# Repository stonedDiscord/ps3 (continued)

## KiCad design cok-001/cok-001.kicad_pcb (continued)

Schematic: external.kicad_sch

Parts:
C3246: 47u 25V; CP_EIA-3528-15_AVX-H
C3247: 47u 25V; CP_EIA-7132-28_AVX-C
D3201, D3202, D3203, D3204, D3205, D3206, D3207, D3208: Dual diode; SC-82AA
FB3206: FerriteBead_Small
J3208: 凸; Molex_SlimStack_55560-0801_2x40_P0.50mm_Vertical
J3209: ATA Power; JST_PH_S4B-PH-SM4-TB_1x04-1MP_P2.00mm_Horizontal
J3219: for Multi_Card_Board; Hirose_FH12-15S-0.5SH_1x15-1MP_P0.50mm_Horizontal
J3221: IMSA-9637S-60Y801; Hirose_FH12-60S
LF3204: 0uH
Q3201: DTC144E; SOT-323_SC-70
R3211, R3212, R3213, R3214, R3215, R3216, R3217, R3218, R3219, R3220, R3221, R3222, R3223, R3224, R3225, R3226, R3227, R3231, R3282, R3283, R3284, R3285, R3286, R3287, R3298: 0; R_0402_1005Metric
R3228: 82; R_0402_1005Metric
R3229, R3230, R3232: 22; R_0402_1005Metric
R3233, R3234, R3236, R3237, R3238, R3239: 33; R_0402_1005Metric
R3240, R3253: 0; R_0603_1608Metric
R3241: XX; R_0603_1608Metric; not fitted
R3247: 10k; R_0402_1005Metric
R3297: 0; R_0805_2012Metric
RN3201, RN3202, RN3203, RN3204, RN3205, RN3206, RN3207, RN3208, RN3209, RN3210, RN3211: 56; R_Array_Convex_4x0402
TP3222: TestPoint; TestPoint_Pad_1.0x1.0mm

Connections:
+3.3V_BRIDGE: R3240.1; also elsewhere on the board
/External/SB_USB2_DM_32: J3219.4, LF3204.4
/External/SB_USB2_DP_32: J3219.3, LF3204.2
/External/XSB_CBLID: J3221.43, Q3201.1 (B)
BD_LED: J3221.50; also elsewhere on the board
DISC_CHUCK: R3286.1; also elsewhere on the board
DISC_IN: R3287.1
DISC_IN_MECHA: J3221.55; also elsewhere on the board
DISC_OUT8_SW: R3285.1
DISC_OUT12_SW: R3284.1
EJECT_MECHA: J3221.56; also elsewhere on the board
GND: C3246.2, C3247.2, D3201.1 (A1), D3201.2 (A2), D3202.1 (A1), D3202.2 (A2), D3203.1 (A1), D3203.2 (A2), D3204.1 (A1), D3204.2 (A2), D3205.1 (A1), D3205.2 (A2), D3206.1 (A1), D3206.2 (A2), D3207.1 (A1), D3207.2 (A2), D3208.1 (A1), D3208.2 (A2), J3208.2, J3208.11, J3208.12, J3208.18, J3208.21, J3208.22, J3208.35, J3208.36, J3208.47, J3208.48, J3208.61, J3208.62, J3208.71, J3208.72, J3209.2, J3209.3, J3209.MP (MountPin), J3219.1, J3219.2, J3219.5, J3219.6, J3219.8, J3219.13, J3219.15, J3219.MP (MountPin), J3221.2, J3221.19, J3221.21, J3221.23, J3221.25, J3221.27, J3221.29, J3221.38, J3221.42, J3221.51, J3221.59, Q3201.2 (E), R3247.1; also elsewhere on the board
MC_ALIVE: R3282.1; also elsewhere on the board
MC_P_OFF_REQ: J3221.48; also elsewhere on the board
MC_RESERVED: J3221.49
MECHA_INT: R3283.1; also elsewhere on the board
unnamed: J3208.1, R3241.2
unnamed: C3247.1, J3209.1, R3297.2
unnamed: C3246.1, J3209.4
unnamed: J3219.7, R3253.2
unnamed: FB3206.2, J3219.9, J3219.10, J3219.11, J3219.12
unnamed: J3221.1, R3211.2
unnamed: J3221.3, R3227.2
unnamed: J3221.4, R3226.2
unnamed: J3221.5, R3225.2
unnamed: J3221.6, R3224.2
unnamed: J3221.7, R3223.2
unnamed: J3221.8, R3222.2
unnamed: J3221.9, R3221.2
unnamed: J3221.10, R3220.2
unnamed: J3221.11, R3219.2
unnamed: J3221.12, R3218.2
unnamed: J3221.13, R3217.2
unnamed: J3221.14, R3216.2
unnamed: J3221.15, R3215.2
unnamed: J3221.16, R3214.2
unnamed: J3221.17, R3213.2
unnamed: J3221.18, R3212.2
unnamed: J3221.20, R3232.2
unnamed: J3221.22, R3231.2
unnamed: J3221.24, R3230.2
unnamed: J3221.26, R3229.2
unnamed: J3221.28, R3228.2
unnamed: J3221.31, R3239.2
unnamed: J3221.32, R3238.2
unnamed: J3221.33, R3237.2
unnamed: J3221.34, R3236.2
unnamed: J3221.36, R3234.2
unnamed: J3221.37, R3233.2
unnamed: J3221.44, TP3222.1 (1_1)
unnamed: J3221.46, R3283.2
unnamed: J3221.47, R3282.2
unnamed: J3221.52, R3287.2
unnamed: J3221.54, R3286.2
unnamed: J3221.57, R3285.2
unnamed: J3221.58, R3284.2
unnamed: R3240.2, R3241.1
PHOTO_LED: J3221.53
SB_ATA0_CS0: R3238.1
SB_ATA0_CS1: R3239.1
SB_ATA0_DA0: R3236.1
SB_ATA0_DA1: R3234.1; also elsewhere on the board
SB_ATA0_DA2: R3237.1
SB_ATA0_DASP: J3221.30
SB_ATA0_DD0: D3201.3 (K1), R3226.1; also elsewhere on the board
SB_ATA0_DD1: D3201.4 (K2), R3224.1; also elsewhere on the board
SB_ATA0_DD2: D3203.3 (K1), R3222.1; also elsewhere on the board
SB_ATA0_DD3: D3203.4 (K2), R3220.1; also elsewhere on the board
SB_ATA0_DD4: D3204.3 (K1), R3218.1; also elsewhere on the board
SB_ATA0_DD5: D3204.4 (K2), R3216.1; also elsewhere on the board
SB_ATA0_DD6: D3205.3 (K1), R3214.1; also elsewhere on the board
SB_ATA0_DD7: D3205.4 (K2), R3212.1; also elsewhere on the board
SB_ATA0_DD8: D3207.4 (K2), R3213.1; also elsewhere on the board
SB_ATA0_DD9: D3207.3 (K1), R3215.1; also elsewhere on the board
SB_ATA0_DD10: D3206.4 (K2), R3217.1; also elsewhere on the board
SB_ATA0_DD11: D3202.4 (K2), R3219.1; also elsewhere on the board
SB_ATA0_DD12: D3202.3 (K1), R3221.1; also elsewhere on the board
SB_ATA0_DD13: D3206.3 (K1), R3223.1; also elsewhere on the board
SB_ATA0_DD14: D3208.4 (K2), R3225.1; also elsewhere on the board
SB_ATA0_DD15: D3208.3 (K1), R3227.1; also elsewhere on the board
SB_ATA0_DIOR: R3230.1
SB_ATA0_DIOW: R3229.1
SB_ATA0_DMACK: R3232.1
SB_ATA0_DMARQ: R3228.1
SB_ATA0_INTRQ: R3233.1; also elsewhere on the board
SB_ATA0_IORDY: R3231.1
SB_ATA0_PDIAG: Q3201.3 (C)
SB_PCI0_CLK: J3208.20; also elsewhere on the board
SB_PCI_AD0: J3208.75, RN3204.8 (R1.2); also elsewhere on the board
SB_PCI_AD0_SB: RN3204.1 (R1.1); also elsewhere on the board
SB_PCI_AD1: J3208.78, RN3209.2 (R2.1); also elsewhere on the board
SB_PCI_AD1_SB: RN3209.7 (R2.2); also elsewhere on the board
SB_PCI_AD2: J3208.73, RN3204.7 (R2.2); also elsewhere on the board
SB_PCI_AD2_SB: RN3204.2 (R2.1); also elsewhere on the board
SB_PCI_AD3: J3208.76, RN3209.3 (R3.1); also elsewhere on the board
SB_PCI_AD3_SB: RN3209.6 (R3.2); also elsewhere on the board
SB_PCI_AD4: J3208.69, RN3204.6 (R3.2); also elsewhere on the board
SB_PCI_AD4_SB: RN3204.3 (R3.1); also elsewhere on the board
SB_PCI_AD5: J3208.74, RN3209.4 (R4.1); also elsewhere on the board
SB_PCI_AD5_SB: RN3209.5 (R4.2); also elsewhere on the board
SB_PCI_AD6: J3208.67, RN3204.5 (R4.2); also elsewhere on the board
SB_PCI_AD6_SB: RN3204.4 (R4.1); also elsewhere on the board
SB_PCI_AD7: J3208.70, RN3211.1 (R1.1); also elsewhere on the board
SB_PCI_AD7_SB: RN3211.8 (R1.2); also elsewhere on the board
SB_PCI_AD8: J3208.68, RN3211.2 (R2.1); also elsewhere on the board
SB_PCI_AD8_SB: RN3211.7 (R2.2); also elsewhere on the board
SB_PCI_AD9: J3208.63, RN3203.7 (R2.2); also elsewhere on the board
SB_PCI_AD9_SB: RN3203.2 (R2.1); also elsewhere on the board
SB_PCI_AD10: J3208.66, RN3211.3 (R3.1); also elsewhere on the board
SB_PCI_AD10_SB: RN3211.6 (R3.2); also elsewhere on the board
SB_PCI_AD11: J3208.59, RN3203.6 (R3.2); also elsewhere on the board
SB_PCI_AD11_SB: RN3203.3 (R3.1); also elsewhere on the board
SB_PCI_AD12: J3208.64, RN3211.4 (R4.1); also elsewhere on the board
SB_PCI_AD12_SB: RN3211.5 (R4.2); also elsewhere on the board
SB_PCI_AD13: J3208.57, RN3203.5 (R4.2); also elsewhere on the board
SB_PCI_AD13_SB: RN3203.4 (R4.1); also elsewhere on the board
SB_PCI_AD14: J3208.60, RN3210.1 (R1.1); also elsewhere on the board
SB_PCI_AD14_SB: RN3210.8 (R1.2); also elsewhere on the board
SB_PCI_AD15: J3208.55, RN3205.8 (R1.2); also elsewhere on the board
SB_PCI_AD15_SB: RN3205.1 (R1.1); also elsewhere on the board
SB_PCI_AD16: J3208.43; also elsewhere on the board
SB_PCI_AD17: J3208.44, RN3208.3 (R3.1); also elsewhere on the board
SB_PCI_AD17_SB: RN3208.6 (R3.2); also elsewhere on the board
SB_PCI_AD18: J3208.41, RN3202.8 (R1.2); also elsewhere on the board
SB_PCI_AD18_SB: RN3202.1 (R1.1); also elsewhere on the board
SB_PCI_AD19: J3208.42, RN3208.4 (R4.1); also elsewhere on the board
SB_PCI_AD19_SB: RN3208.5 (R4.2); also elsewhere on the board
SB_PCI_AD20: J3208.39, RN3202.7 (R2.2); also elsewhere on the board
SB_PCI_AD20_SB: RN3202.2 (R2.1); also elsewhere on the board
SB_PCI_AD21: J3208.40, RN3207.1 (R1.1); also elsewhere on the board
SB_PCI_AD21_SB: RN3207.8 (R1.2); also elsewhere on the board
SB_PCI_AD22: J3208.37, RN3202.6 (R3.2); also elsewhere on the board
SB_PCI_AD22_SB: RN3202.3 (R3.1); also elsewhere on the board
SB_PCI_AD23: J3208.38, RN3207.2 (R2.1); also elsewhere on the board
SB_PCI_AD23_SB: RN3207.7 (R2.2); also elsewhere on the board
SB_PCI_AD24: J3208.31, RN3202.5 (R4.2); also elsewhere on the board
SB_PCI_AD24_SB: RN3202.4 (R4.1); also elsewhere on the board
SB_PCI_AD25: J3208.32, RN3207.4 (R4.1); also elsewhere on the board
SB_PCI_AD25_SB: RN3207.5 (R4.2); also elsewhere on the board
SB_PCI_AD26: J3208.29, RN3201.8 (R1.2); also elsewhere on the board
SB_PCI_AD26_SB: RN3201.1 (R1.1); also elsewhere on the board
SB_PCI_AD27: J3208.30, RN3206.1 (R1.1); also elsewhere on the board
SB_PCI_AD27_SB: RN3206.8 (R1.2); also elsewhere on the board
SB_PCI_AD28: J3208.27, RN3201.7 (R2.2); also elsewhere on the board
SB_PCI_AD28_SB: RN3201.2 (R2.1); also elsewhere on the board
SB_PCI_AD29: J3208.28, RN3206.2 (R2.1); also elsewhere on the board
SB_PCI_AD29_SB: RN3206.7 (R2.2); also elsewhere on the board
SB_PCI_AD30: J3208.25, RN3201.6 (R3.2); also elsewhere on the board
SB_PCI_AD30_SB: RN3201.3 (R3.1); also elsewhere on the board
SB_PCI_AD31: J3208.26, RN3206.3 (R3.1); also elsewhere on the board
SB_PCI_AD31_SB: RN3206.6 (R3.2); also elsewhere on the board
SB_PCI_PAR: J3208.53, RN3205.7 (R2.2); also elsewhere on the board
SB_PCI_PAR_SB: RN3205.2 (R2.1); also elsewhere on the board
SB_PIO8: J3208.10; also elsewhere on the board
SB_PIO9: J3208.8; also elsewhere on the board
SB_PIO10: J3208.6; also elsewhere on the board
SB_PIO11: J3208.4; also elsewhere on the board
SB_PIO12: J3208.9; also elsewhere on the board
SB_PIO13: J3208.7; also elsewhere on the board
SB_PIO14: J3208.5; also elsewhere on the board
SB_PIO15: J3208.3; also elsewhere on the board
SB_SIO0_RXD: J3208.77; also elsewhere on the board
SB_SIO0_TXD: J3208.79; also elsewhere on the board
SW_PCI: J3208.80; also elsewhere on the board
~MC_DET: J3219.14; also elsewhere on the board
~SB_ATA0_RESET: R3211.1; also elsewhere on the board
~SB_PCI_CBE0_SB: RN3203.1 (R1.1); also elsewhere on the board
~SB_PCI_CBE0: J3208.65, RN3203.8 (R1.2); also elsewhere on the board
~SB_PCI_CBE1_SB: RN3209.8 (R1.2); also elsewhere on the board
~SB_PCI_CBE1: J3208.58, RN3209.1 (R1.1); also elsewhere on the board
~SB_PCI_CBE2_SB: RN3208.7 (R2.2); also elsewhere on the board
~SB_PCI_CBE2: J3208.46, RN3208.2 (R2.1); also elsewhere on the board
~SB_PCI_CBE3_SB: RN3207.6 (R3.2); also elsewhere on the board
~SB_PCI_CBE3: J3208.34, RN3207.3 (R3.1); also elsewhere on the board
~SB_PCI_DEVSEL_SB: RN3210.5 (R4.2); also elsewhere on the board
~SB_PCI_DEVSEL: J3208.52, RN3210.4 (R4.1); also elsewhere on the board
~SB_PCI_FRAME: J3208.45; also elsewhere on the board
~SB_PCI_GNT0: J3208.19
~SB_PCI_GNT1_SB: RN3206.5 (R4.2); also elsewhere on the board
~SB_PCI_GNT1: RN3206.4 (R4.1); also elsewhere on the board
~SB_PCI_INTA: J3208.13; also elsewhere on the board
~SB_PCI_INTB: J3208.14
~SB_PCI_INTC: J3208.15; also elsewhere on the board
~SB_PCI_INTD: J3208.16
~SB_PCI_IRDY_SB: RN3208.8 (R1.2); also elsewhere on the board
~SB_PCI_IRDY: J3208.50, RN3208.1 (R1.1); also elsewhere on the board
~SB_PCI_PERR_SB: RN3210.6 (R3.2); also elsewhere on the board
~SB_PCI_PERR: J3208.54, RN3210.3 (R3.1); also elsewhere on the board
~SB_PCI_PME: J3208.23; also elsewhere on the board
~SB_PCI_REQ0: J3208.24
~SB_PCI_RST_SB: RN3201.4 (R4.1); also elsewhere on the board
~SB_PCI_RST: J3208.17, RN3201.5 (R4.2)
~SB_PCI_SERR_SB: RN3210.7 (R2.2); also elsewhere on the board
~SB_PCI_SERR: J3208.56, RN3210.2 (R2.1); also elsewhere on the board
~SB_PCI_STOP_SB: RN3205.3 (R3.1); also elsewhere on the board
~SB_PCI_STOP: J3208.51, RN3205.6 (R3.2); also elsewhere on the board
~SB_PCI_TRDY_SB: RN3205.4 (R4.1); also elsewhere on the board
~SB_PCI_TRDY: J3208.49, RN3205.5 (R4.2); also elsewhere on the board
~SB_RESET: R3253.1; also elsewhere on the board

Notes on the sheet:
PCI0
ATA0 for BD

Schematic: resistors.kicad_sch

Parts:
C1103: 0.001u 50V; C_0402_1005Metric
C1104: 0.1u 10V; C_0402_1005Metric
C1106, C1444, C1445, C1446, C1447, C1448, C1449, C1450, C1451, C1452, C1453, C1454: 1u; C_0402_1005Metric
C1117: 270p; C_0402_1005Metric
C1136, C1137, C1152, C1153, C1154, C1155, C1181, C1182, C1186, C1187: 0.1u; C_0402_1005Metric
C1160: 0.01u; C_0402_1005Metric
C1488, C1491, C1492: 100p; C_0402_1005Metric
L1101: 270nH; L_0603_1608Metric
Q1101, Q1102: DTC144E; SOT-323_SC-70
R1106, R1107, R1116, R1144, R1155, R1157, R1159, R1161, R1162, R1163: 100; R_0402_1005Metric
R1108, R1109, R1118, R1119, R1120, R1121, R1127, R1128: 49.9; R_0402_1005Metric
R1112, R1114: 95.3; R_0402_1005Metric
R1113, R1115: 191; R_0402_1005Metric
R1129, R1131: 56.2; R_0402_1005Metric
R1130, R1132: 137; R_0402_1005Metric
R1136, R1170: 0; R_0402_1005Metric
R1137, R1143, R1147, R1148, R1150, R1152, R1166, R1167, R1168, R1169, R1173, R1174: 10k; R_0402_1005Metric
R1158, R1160, R1164, R1165: 10k; R_0402_1005Metric; not fitted
RN1101: 10k; R_Array_Convex_4x0402
TP1101, TP1102, TP1103, TP1104, TP1105, TP1106, TP1107, TP1108, TP1117, TP1118, TP1119, TP1120: TestPoint; TestPoint_Pad_1.0x1.0mm
U1101: ADT7461A0002RMZR; MSOP-8_2.9x4mm_P0.65mm

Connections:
+1.2V_MC2_VDDIO: C1444.1, C1445.1, C1446.1, C1447.1, C1448.1, C1449.1, C1450.1, C1451.1, C1452.1, C1453.1, C1454.1, R1137.2, R1148.2, R1150.2, R1152.2, R1158.2, R1160.2, R1164.2, R1165.2, R1169.2, R1173.2, R1174.2, RN1101.5 (R4.2), RN1101.6 (R3.2), RN1101.7 (R2.2), RN1101.8 (R1.2); also elsewhere on the board
+1.2V_YC_RC_VDDIO: C1136.1, C1137.1, C1152.1, C1153.1, C1154.1, C1155.1, C1181.1, C1182.1, C1186.1, C1187.1, R1108.2, R1109.2, R1112.2, R1114.2, R1118.2, R1119.2, R1120.2, R1121.2, R1127.2, R1128.2, R1129.2, R1131.2; also elsewhere on the board
+1.5V_BE_THERMAL_VDDA: C1160.1, R1170.2
+1.6V_BE_VDDA: L1101.1; also elsewhere on the board
+3.3V_THERMAL: C1104.1, U1101.1 (Vdd); also elsewhere on the board
BE_IN: R1165.1, R1167.2
BE_PLL_VDDA: C1106.1, C1117.1, L1101.2, R1170.1; also elsewhere on the board
BE_POWGOOD: C1491.1, R1143.2, TP1108.1 (1_1); also elsewhere on the board
BE_P_L_BYPASS: R1169.1
BE_RC_RLOAD0: R1127.1; also elsewhere on the board
BE_RC_RLOAD1: R1128.1
BE_RC_VOLGND0: C1181.2, R1130.1; also elsewhere on the board
BE_RC_VOLGND1: C1182.2, R1132.1; also elsewhere on the board
BE_RC_VOLREF0: R1129.1, R1130.2, TP1119.1 (1_1); also elsewhere on the board
BE_RC_VOLREF1: R1131.1, R1132.2, TP1120.1 (1_1)
BE_SCAN_ENA: R1116.2
BE_SPI_CLK: R1173.1
BE_SPI_CTL0: R1162.1
BE_SPI_CTL1: R1163.1; also elsewhere on the board
BE_SPI_DO: R1174.1; also elsewhere on the board
BE_SYS_CONF0: R1155.2; also elsewhere on the board
BE_SYS_CONF1: R1157.2; also elsewhere on the board
BE_SYS_CONF2: R1158.1, R1159.2; also elsewhere on the board
BE_SYS_CONF3: R1160.1, R1161.2; also elsewhere on the board
BE_TBEN: R1152.1; also elsewhere on the board
BE_TCK: RN1101.3 (R3.1), TP1105.1 (1_1)
BE_TDI: RN1101.2 (R2.1), TP1104.1 (1_1); also elsewhere on the board
BE_TDO: TP1103.1 (1_1); also elsewhere on the board
BE_THR_ALRT: Q1101.1 (B), R1164.1, R1166.2; also elsewhere on the board
BE_TMS: RN1101.1 (R1.1), TP1106.1 (1_1); also elsewhere on the board
BE_TRG_IN: R1144.2; also elsewhere on the board
BE_TRG_OUT: R1147.2; also elsewhere on the board
BE_Y0_DQ0_RLOAD: R1118.1; also elsewhere on the board
BE_Y0_DQ2_RLOAD: R1120.1; also elsewhere on the board
BE_Y0_DQC_ROLREF: R1108.1; also elsewhere on the board
BE_Y0_DQC_VOLGND: C1136.2, R1113.1; also elsewhere on the board
BE_Y0_DQC_VOLREF: R1112.1, R1113.2, TP1117.1 (1_1); also elsewhere on the board
BE_Y1_DQ0_RLOAD: R1119.1; also elsewhere on the board
BE_Y1_DQ2_RLOAD: R1121.1; also elsewhere on the board
BE_Y1_DQC_ROLREF: R1109.1; also elsewhere on the board
BE_Y1_DQC_VOLGND: C1137.2, R1115.1; also elsewhere on the board
BE_Y1_DQC_VOLREF: R1114.1, R1115.2, TP1118.1 (1_1); also elsewhere on the board
GND: C1104.2, C1106.2, C1117.2, C1152.2, C1153.2, C1154.2, C1155.2, C1160.2, C1186.2, C1187.2, C1444.2, C1445.2, C1446.2, C1447.2, C1448.2, C1449.2, C1450.2, C1451.2, C1452.2, C1453.2, C1454.2, C1488.2, C1491.2, C1492.2, Q1101.2 (E), Q1102.2 (E), R1116.1, R1143.1, R1144.1, R1147.1, R1155.1, R1157.1, R1159.1, R1161.1, R1162.2, R1163.2, R1166.1, R1167.1, R1168.1, U1101.5 (GND); also elsewhere on the board
unnamed: C1103.2, R1106.2, U1101.2 (D+)
unnamed: C1103.1, R1107.1, U1101.3 (D-)
SB_CHKSTP_OUT: Q1102.1 (B); also elsewhere on the board
STI_THERMAL0: R1106.1; also elsewhere on the board
STI_THERMAL1: R1107.2
THR_I2C_SCL: U1101.8 (SCLK); also elsewhere on the board
THR_I2C_SDA: U1101.7 (SDATA); also elsewhere on the board
~BE_CHKSTP_IN: C1492.1, Q1102.3 (C), R1148.1; also elsewhere on the board
~BE_CHKSTP_OUT: R1150.1; also elsewhere on the board
~BE_HARD_RESET: C1488.1, R1136.2, TP1101.1 (1_1)
~BE_RESET: R1136.1, R1168.2, TP1102.1 (1_1)
~BE_SPI_CS: R1137.1; also elsewhere on the board
~BE_TRST: RN1101.4 (R4.1), TP1107.1 (1_1); also elsewhere on the board
~SYS_THR_ALRT: Q1101.3 (C); also elsewhere on the board
~THRBE_SENS_ALRT: U1101.6 (~ALERT/~THERM2)

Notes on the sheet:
BE THERMAL POWER
JTAG
BE REDWOOD RESISTORS
YRAC REFERENCE RESISTORS (Y0)
MC2 VDDIO BYPASSING
BE Temperature Monitor
BE PLL VDDA/GNDA

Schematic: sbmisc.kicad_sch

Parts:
C3148, C3151: XX; C_0402_1005Metric; not fitted
C3152: XX; C_0402_1005Metric
C3153: 0.01u; C_0402_1005Metric
C3155: 0.1u 10V; C_0402_1005Metric
Q3101: DTC143ZUA; SOT-323_SC-70
R3092, R3096, R3136, R3162, R3163: 10k; R_0402_1005Metric
R3098, R3102, R3105, R3107, R3119, R3120, R3121, R3131, R3132, R3138, R3143: XX; R_0402_1005Metric; not fitted
R3099, R3103, R3137, R3142, R3144, R3145, R3146: 4700; R_0402_1005Metric
R3109, R3113, R3118, R3122, R3130: 0; R_0402_1005Metric
TP3031, TP3033, TP3034, TP3035, TP3036, TP3037, TP3038, TP3039, TP3040: TestPoint; TestPoint_Pad_1.0x1.0mm
U3101: AD51/007Z; MSOP-8_2.9x4mm_P0.65mm
X3001: ASCO; Oscillator_SMD_Abracon_ASE-4Pin_3.2x2.5mm; not fitted

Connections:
+1.2V_SB_VDDC: R3144.1; also elsewhere on the board
+3.3V_SB_VDDIO: C3148.1, R3099.1, R3103.1, R3119.1, R3131.1, R3137.1, R3142.1, X3001.4 (VDD); also elsewhere on the board
+3.3V_THERMAL: C3155.1, U3101.7 (A0), U3101.8 (V_{DD}); also elsewhere on the board
GND: C3148.2, C3151.2, C3152.2, C3153.2, C3155.2, Q3101.2 (E), R3092.2, R3096.2, R3098.2, R3102.2, R3107.2, R3109.2, R3113.2, R3118.2, R3120.2, R3130.2, R3132.2, R3136.2, R3138.2, R3143.2, R3145.2, R3146.2, R3162.2, R3163.2, U3101.4 (GND), U3101.5 (A2), U3101.6 (A1), X3001.2 (GND); also elsewhere on the board
MECHA_INT: R3163.1; also elsewhere on the board
MK_USB_CLK: R3122.1; also elsewhere on the board
unnamed: C3151.1, R3105.2, R3121.1
unnamed: R3105.1, X3001.3 (OUT)
SB_CHKSTP_IN: Q3101.3 (C); also elsewhere on the board
SB_CHKSTP_OUT: R3092.1; also elsewhere on the board
SB_GBE_CLK: C3152.1; also elsewhere on the board
SB_GBE_RVRX: R3131.2, R3132.1; also elsewhere on the board
SB_GBE_RVTX: R3119.2, R3120.1; also elsewhere on the board
SB_IOP_TRST: R3136.1
SB_PCIHOST: R3137.2; also elsewhere on the board
SB_PEX0_REFCLKN: R3144.2; also elsewhere on the board
SB_PEX0_REFCLKP: R3145.1; also elsewhere on the board
SB_PEX_AFIN: R3146.1; also elsewhere on the board
SB_PEX_AMOUT: C3153.1; also elsewhere on the board
SB_PIO8: TP3033.1 (1_1); also elsewhere on the board
SB_PIO9: TP3034.1 (1_1); also elsewhere on the board
SB_PIO10: TP3035.1 (1_1); also elsewhere on the board
SB_PIO11: TP3036.1 (1_1); also elsewhere on the board
SB_PIO12: TP3037.1 (1_1); also elsewhere on the board
SB_PIO13: TP3038.1 (1_1); also elsewhere on the board
SB_PIO14: TP3039.1 (1_1); also elsewhere on the board
SB_PIO15: TP3040.1 (1_1); also elsewhere on the board
SB_PLLBYPASS: R3130.1; also elsewhere on the board
SB_TAPSELECT: R3113.1
SB_TESTIN0: R3098.1
SB_TESTIN1: R3102.1
SB_TESTIN2: R3107.1
SB_TESTIN7: R3138.1; also elsewhere on the board
SB_TESTMOD: R3118.1
SB_TRG_IN: R3162.1; also elsewhere on the board
SB_TRG_OUT: R3096.1; also elsewhere on the board
SB_USB_CLK: R3121.2, R3122.2, TP3031.1 (1_1); also elsewhere on the board
THR_I2C_SCL: U3101.2 (SCL); also elsewhere on the board
THR_I2C_SDA: U3101.1 (SDA); also elsewhere on the board
~BE_CHKSTP_OUT: Q3101.1 (B); also elsewhere on the board
~SB_INT: R3142.2, R3143.1; also elsewhere on the board
~SB_MOD0: R3099.2
~SB_MOD1: R3103.2
~SB_MOD2: R3109.1

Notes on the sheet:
SB MISC Signals
TEST SW
GbE Bit Reverce
ATA CLOCK Select ⋆
GbE CLOCK ⋆
PCI-Ex
MODE SELECT
USB CLOCK Select
PIO

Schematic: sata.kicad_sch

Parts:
C3404, C3405, C3408, C3417: 0.1u 10V; C_0402_1005Metric
C3409, C3410, C3412, C3413, C3414, C3415: 0.01u; C_0402_1005Metric
C3418, C3419: 15p 50V; C_0402_1005Metric
C3421: XX 10V; C_0402_1005Metric; not fitted
D3401: CL-196TLY-CD-T; D_0603_1608Metric
FB3401: 0uH; L_0603_1608Metric
FB3402: FerriteBead_Small; L_0603_1608Metric
J3401: Conn_01x22_Pin; SATA
L3401, L3402: L_Iron_Coupled_Small_1243; L_CommonModeChoke_Coilcraft_0805USB
Q3401, Q3402, Q3403, Q3404: DTC144E; SOT-323_SC-70
R3402, R3403, R3404, R3405, R3406, R3410, R3419, R3420, R3421, R3422, R3423, R3424, R3425, R3426, R3427, R3428, R3429, R3430, R3431, R3432, R3433, R3434: 33; R_0402_1005Metric
R3407, R3408, R3409, R3435, R3436, R3437: 22; R_0402_1005Metric
R3411, R3412, R3438, R3439, R3451, R3462: 10k; R_0402_1005Metric
R3413: 5600; R_0402_1005Metric
R3414, R3415, R3416: 82; R_0402_1005Metric
R3417: 4700; R_0402_1005Metric
R3441, R3442, R3443, R3444, R3445, R3446, R3447, R3448, R3454, R3460, R3466, R3467, R3468, R3471: XX; R_0402_1005Metric; not fitted
R3449, R3450, R3455, R3469: 0; R_0402_1005Metric
R3452: 12k; R_0402_1005Metric
R3458: 100; R_0402_1005Metric
R3459: 330; R_0402_1005Metric
R3461: 220; R_0402_1005Metric
TH3401: Polyfuse; Fuse_1210_3225Metric
TP3401, TP3402: TestPoint; TestPoint_Pad_D1.5mm
U3401: LQFP-64_10x10mm_P0.5mm
Y3402: 25MHz; Crystal_SMD_Abracon_ABM8G-4Pin_3.2x2.5mm

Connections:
+5V_HDD: TH3401.1; also elsewhere on the board
GND: C3404.2, C3405.2, C3408.2, C3417.2, C3418.1, C3419.1, C3421.2, J3401.MP (Shield), J3401.P4 (GND), J3401.P5 (GND), J3401.P6 (GND), J3401.P10 (GND), J3401.P11 (Staggered), J3401.P12 (GND), J3401.S1 (GND), J3401.S4 (GND), J3401.S7 (GND), Q3401.2 (E), Q3402.2 (E), Q3403.2 (E), Q3404.2 (E), R3411.2, R3412.2, R3413.2, R3443.1, R3447.1, R3452.2, R3454.2, R3455.2, R3466.2, U3401.8 (GND), U3401.42 (GND), U3401.57 (GND), Y3402.2; also elsewhere on the board
unnamed: C3404.1, C3408.1, U3401.9 (VDD), U3401.41 (VDD), U3401.56 (VDD)
unnamed: C3405.1, FB3401.1, R3438.1, R3439.1, R3441.1, R3442.1, R3444.1, R3445.1, R3446.1, R3448.1, R3449.2, R3450.2, R3451.2, R3467.1, R3468.2, U3401.4 (VDDIO), U3401.44 (VDDIO), Y3402.4
unnamed: C3412.2, L3401.3
unnamed: C3413.2, L3402.3
unnamed: C3414.2, L3401.2
unnamed: C3415.2, L3402.2
unnamed: C3418.2, R3461.2, Y3402.1
unnamed: D3401.2 (A), R3459.1
unnamed: D3401.1 (K), Q3403.3 (C)
unnamed: FB3402.1, TH3401.2
unnamed: C3417.1, FB3402.2, J3401.P7 (5Vp), J3401.P8 (5V), J3401.P9 (5V)
unnamed: J3401.S2 (A+), L3401.4
unnamed: J3401.S3 (A-), L3401.1
unnamed: J3401.S6 (B+), L3402.1
unnamed: J3401.S5 (B-), L3402.4
unnamed: Q3401.1 (B), R3438.2
unnamed: Q3402.3 (C), Q3403.1 (B), R3462.1
unnamed: Q3404.1 (B), R3469.1, R3471.2
unnamed: Q3404.3 (C), R3471.1
unnamed: R3413.1, R3416.2, R3437.1
unnamed: R3414.2, R3435.1
unnamed: R3415.2, R3417.2, R3436.1
unnamed: R3452.1, R3458.2
unnamed: R3454.1, U3401.21 (ATAIOSEL)
unnamed: R3455.1, U3401.19 (CFNG1)
unnamed: R3449.1, U3401.20 (CFNG2)
unnamed: R3450.1, U3401.18 (CNFG0)
unnamed: R3403.2, U3401.48 (H_CS0_n)
unnamed: R3402.2, U3401.47 (H_CS1_n)
unnamed: R3405.2, U3401.50 (H_DA0)
unnamed: R3406.2, U3401.51 (H_DA1)
unnamed: R3404.2, U3401.49 (H_DA2)
unnamed: R3420.2, U3401.62 (H_DD0)
unnamed: R3422.2, U3401.64 (H_DD1)
unnamed: R3424.2, U3401.2 (H_DD2)
unnamed: R3426.2, U3401.5 (H_DD3)
unnamed: R3428.2, U3401.7 (H_DD4)
unnamed: R3430.2, U3401.11 (H_DD5)
unnamed: R3432.2, U3401.13 (H_DD6)
unnamed: R3434.2, U3401.15 (H_DD7)
unnamed: R3433.2, U3401.14 (H_DD8)
unnamed: R3431.2, U3401.12 (H_DD9)
unnamed: R3429.2, U3401.10 (H_DD10)
unnamed: R3427.2, U3401.6 (H_DD11)
unnamed: R3425.2, U3401.3 (H_DD12)
unnamed: R3423.2, U3401.1 (H_DD13)
unnamed: R3421.2, U3401.63 (H_DD14)
unnamed: R3419.2, U3401.61 (H_DD15)
unnamed: R3408.2, U3401.58 (H_DIOR_n)
unnamed: R3409.2, U3401.59 (H_DIOW_n)
unnamed: R3407.2, U3401.54 (H_DMACK_n)
unnamed: R3437.2, U3401.60 (H_DMARQ)
unnamed: R3435.2, U3401.53 (H_INTRQ)
unnamed: R3436.2, U3401.55 (H_IORDY)
unnamed: C3421.1, R3410.2, R3466.1, R3467.2, U3401.16 (H_RESET_n)
unnamed: R3458.1, U3401.26 (ISET)
unnamed: C3413.1, U3401.28 (RX_M)
unnamed: C3415.1, U3401.27 (RX_P)
unnamed: R3448.2, U3401.33 (T0)
unnamed: R3439.2, R3447.2, U3401.34 (T1)
unnamed: R3446.2, U3401.35 (T2)
unnamed: R3445.2, U3401.36 (T3)
unnamed: R3444.2, U3401.37 (T4)
unnamed: R3443.2, U3401.38 (T5)
unnamed: R3442.2, U3401.39 (T6)
unnamed: R3441.2, R3469.2, U3401.40 (T7)
unnamed: C3414.1, U3401.31 (TX_M)
unnamed: C3412.1, U3401.32 (TX_P)
unnamed: TP3402.1 (1_1), U3401.43 (UAI)
unnamed: TP3401.1 (1_1), U3401.45 (UAO)
unnamed: C3409.1, C3410.1, FB3401.2, U3401.24 (VAA1), U3401.29 (VAA2)
unnamed: C3409.2, C3410.2, U3401.25 (VSS1), U3401.30 (VSS2)
unnamed: C3419.2, R3460.2, R3468.1, U3401.22 (XTALIN/OSC), Y3402.3
unnamed: R3460.1, R3461.1, U3401.23 (XTALOUT)
SB_ATA1_DA0: R3405.1
SB_ATA1_DA1: R3406.1; also elsewhere on the board
SB_ATA1_DA2: R3404.1
SB_ATA1_DD0: R3420.1; also elsewhere on the board
SB_ATA1_DD1: R3422.1; also elsewhere on the board
SB_ATA1_DD2: R3424.1; also elsewhere on the board
SB_ATA1_DD3: R3426.1; also elsewhere on the board
SB_ATA1_DD4: R3428.1; also elsewhere on the board
SB_ATA1_DD5: R3430.1; also elsewhere on the board
SB_ATA1_DD6: R3432.1; also elsewhere on the board
SB_ATA1_DD7: R3411.1, R3434.1; also elsewhere on the board
SB_ATA1_DD8: R3433.1; also elsewhere on the board
SB_ATA1_DD9: R3431.1; also elsewhere on the board
SB_ATA1_DD10: R3429.1; also elsewhere on the board
SB_ATA1_DD11: R3427.1; also elsewhere on the board
SB_ATA1_DD12: R3425.1; also elsewhere on the board
SB_ATA1_DD13: R3423.1; also elsewhere on the board
SB_ATA1_DD14: R3421.1; also elsewhere on the board
SB_ATA1_DD15: R3419.1; also elsewhere on the board
SB_ATA1_DMARQ: R3416.1
SB_ATA1_INTRQ: R3412.1, R3414.1; also elsewhere on the board
SB_ATA1_IORDY: R3415.1
~SB_ATA1_CS0: R3403.1
~SB_ATA1_CS1: R3402.1
~SB_ATA1_DIOR: R3408.1
~SB_ATA1_DIOW: R3409.1; also elsewhere on the board
~SB_ATA1_DMACK: R3407.1
~SB_ATA1_RESET: R3410.1; also elsewhere on the board
~SB_RESET: R3451.1, U3401.17 (RST_n); also elsewhere on the board

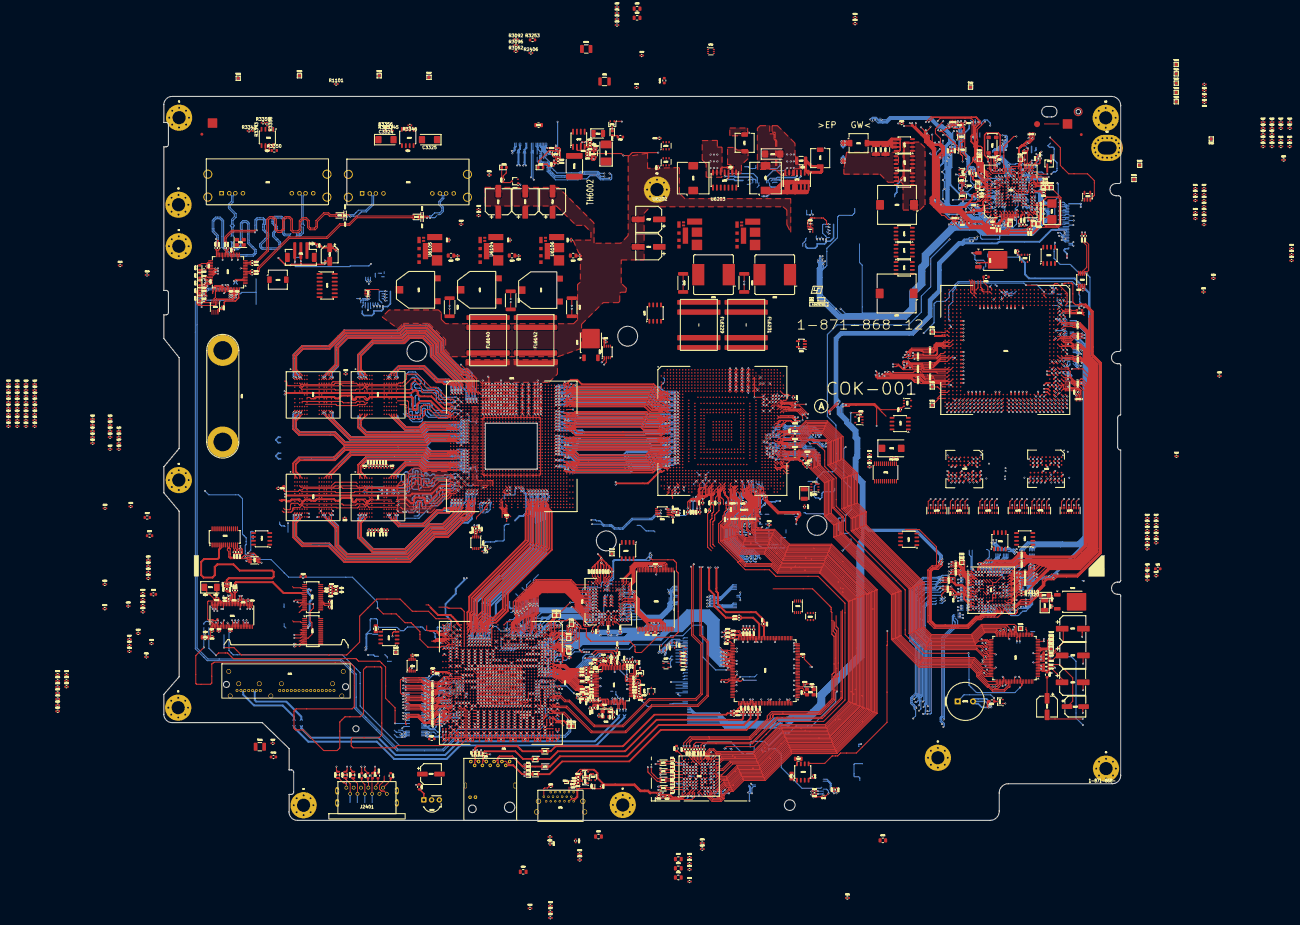
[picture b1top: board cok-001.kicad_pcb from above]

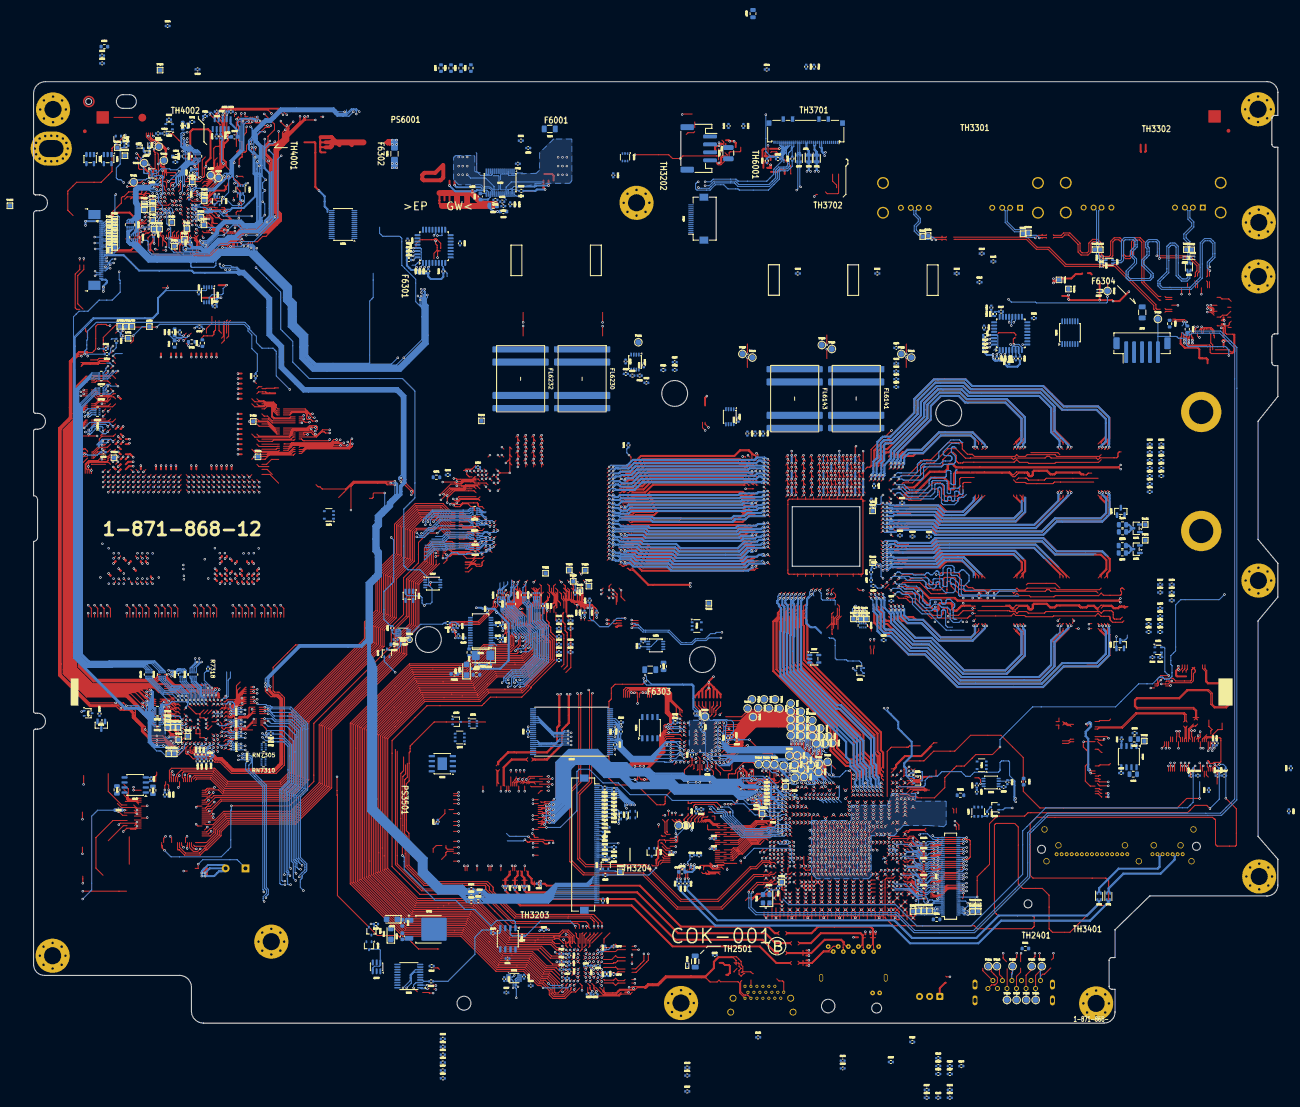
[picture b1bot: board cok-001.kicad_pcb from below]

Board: 2 copper layers, 313.2 x 237.0 mm, 1505 parts (684 on the bottom side), 1962 nets.
